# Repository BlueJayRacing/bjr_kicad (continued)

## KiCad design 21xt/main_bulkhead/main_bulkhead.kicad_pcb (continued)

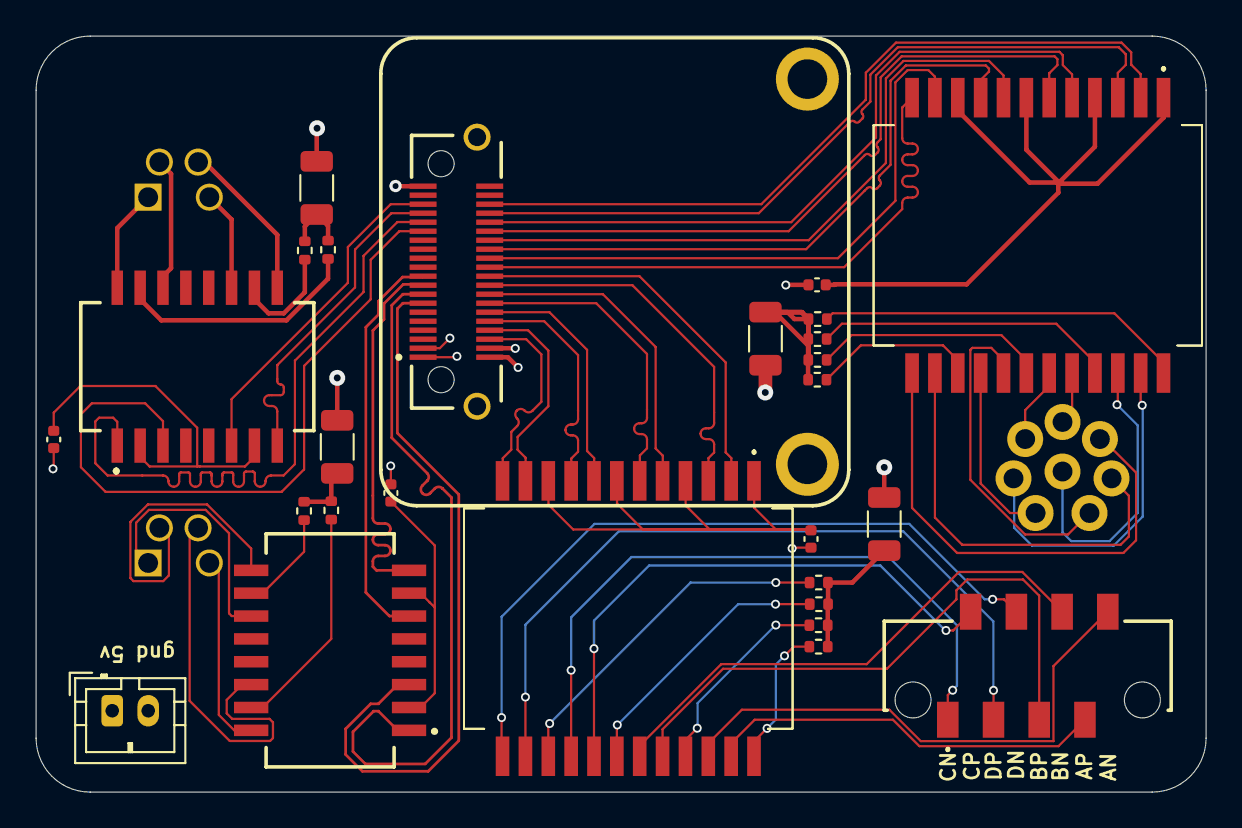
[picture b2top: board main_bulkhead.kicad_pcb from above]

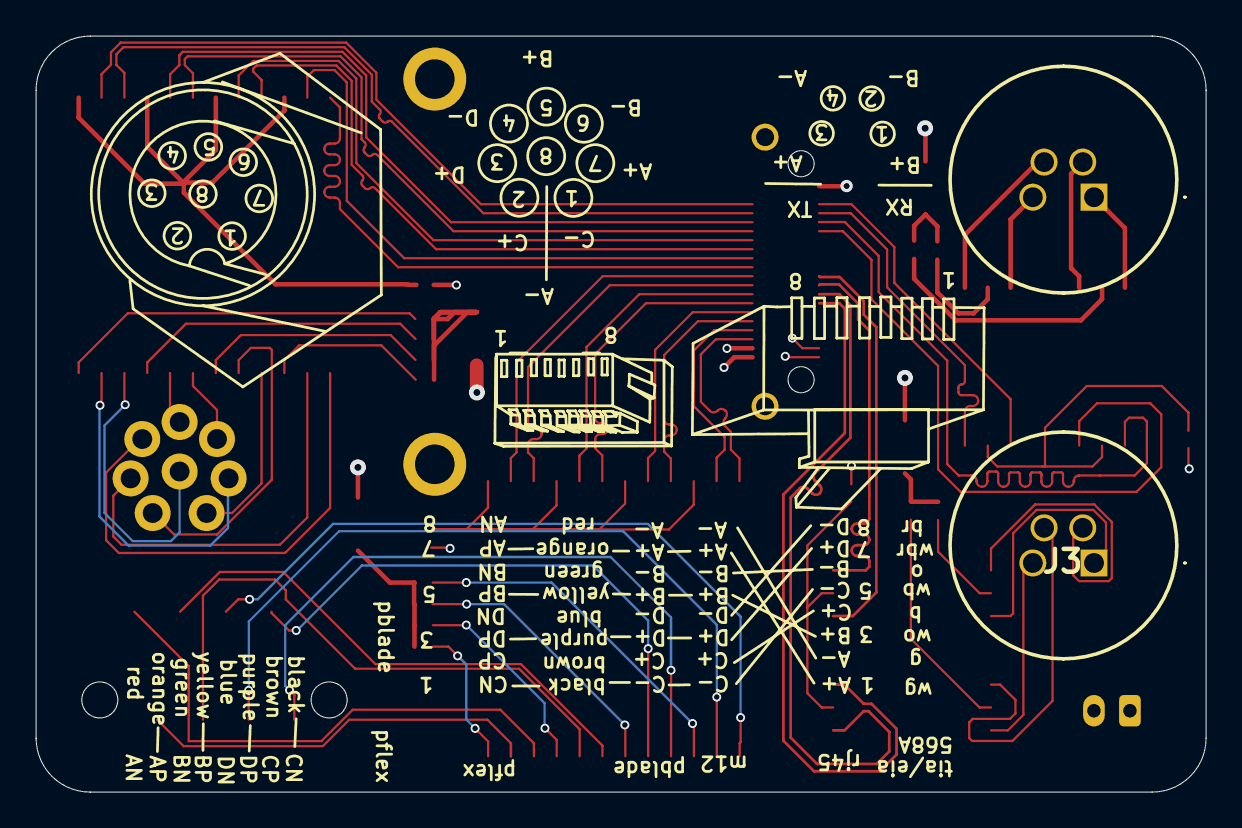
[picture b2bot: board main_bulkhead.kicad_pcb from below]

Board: 4 copper layers, 65.0 x 42.0 mm, 30 parts (3 on the bottom side), 70 nets.

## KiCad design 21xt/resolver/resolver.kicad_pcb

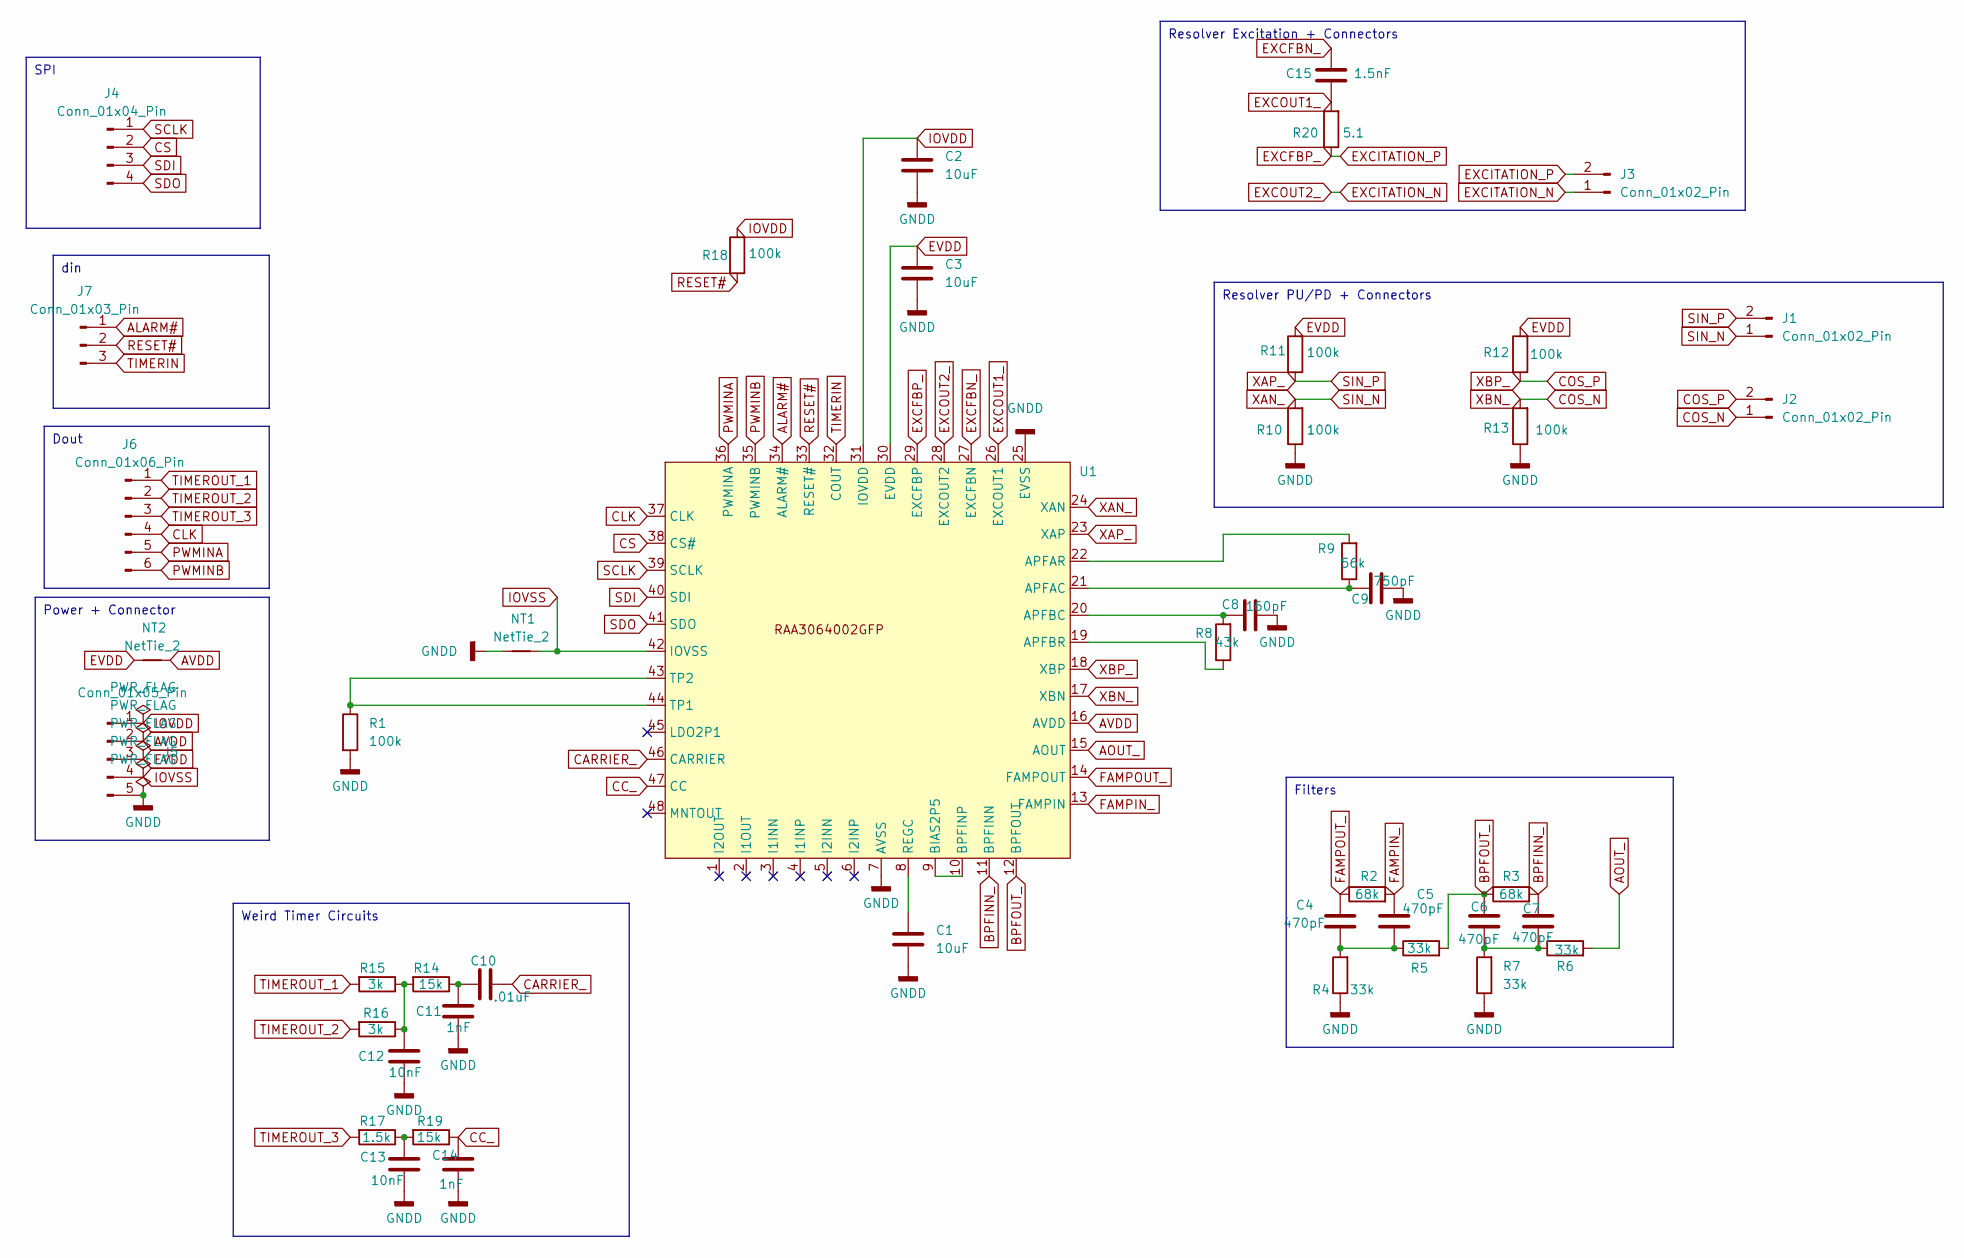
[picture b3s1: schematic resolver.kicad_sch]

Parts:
C1: 10uF; C_0201_0603Metric
C2, C3: 10uF; C_0201_0603Metric_Pad0.64x0.40mm_HandSolder
C4, C5, C6, C7: 470pF; C_0201_0603Metric_Pad0.64x0.40mm_HandSolder
C8: 160pF; C_0201_0603Metric_Pad0.64x0.40mm_HandSolder
C9: 750pF; C_0201_0603Metric_Pad0.64x0.40mm_HandSolder
C10: .01uF; C_0201_0603Metric_Pad0.64x0.40mm_HandSolder
C11, C14: 1nF; C_0201_0603Metric_Pad0.64x0.40mm_HandSolder
C12, C13: 10nF; C_0201_0603Metric_Pad0.64x0.40mm_HandSolder
C15: 1.5nF; C_0201_0603Metric_Pad0.64x0.40mm_HandSolder
J1, J2, J3: Conn_01x02_Pin; PinHeader_1x02_P2.54mm_Vertical
J4: Conn_01x04_Pin; PinHeader_1x04_P2.54mm_Vertical
J5: Conn_01x05_Pin; PinHeader_1x05_P2.54mm_Vertical
J6: Conn_01x06_Pin; PinHeader_1x06_P2.54mm_Vertical
J7: Conn_01x03_Pin; PinHeader_1x03_P2.54mm_Vertical
NT1, NT2: NetTie_2; SolderJumper-2_P1.3mm_Bridged2Bar_Pad1.0x1.5mm
R1, R10, R11, R12, R13, R18: 100k; R_0201_0603Metric
R2, R3: 68k; R_0201_0603Metric
R4, R5, R6, R7: 33k; R_0201_0603Metric
R8: 43k; R_0201_0603Metric
R9: 56k; R_0201_0603Metric
R14, R19: 15k; R_0201_0603Metric
R15, R16: 3k; R_0201_0603Metric
R17: 1.5k; R_0201_0603Metric
R20: 5.1; R_0201_0603Metric
U1: LQFP-48_7x7mm_P0.5mm

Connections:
ALARM#: J7.1, U1.34 (ALARM#)
AOUT_: R6.2, U1.15 (AOUT)
AVDD: J5.2, NT2.2, U1.16 (AVDD)
BPFINN_: C7.1, R3.2, U1.11 (BPFINN)
BPFOUT_: C6.1, R3.1, R5.2, U1.12 (BPFOUT)
CARRIER_: C10.2, U1.46 (CARRIER)
CC_: C14.2, R19.1, U1.47 (CC)
CLK: J6.4, U1.37 (CLK)
COS_N: J2.1, R13.2, U1.17 (XBN)
COS_P: J2.2, R12.1, U1.18 (XBP)
CS: J4.2, U1.38 (CS#)
EVDD: C3.1, J5.3, NT2.1, R11.2, R12.2, U1.30 (EVDD)
EXCFBN_: C15.2, U1.27 (EXCFBN)
EXCFBP_: J3.2, R20.1, U1.29 (EXCFBP)
EXCITATION_N: J3.1, U1.28 (EXCOUT2)
EXCOUT1_: C15.1, R20.2, U1.26 (EXCOUT1)
FAMPIN_: C5.1, R2.2, U1.13 (FAMPIN)
FAMPOUT_: C4.1, R2.1, U1.14 (FAMPOUT)
GNDD: C1.2, C2.2, C3.2, C8.2, C9.2, C11.1, C12.1, C13.1, C14.1, J5.5, NT1.1, R1.2, R4.1, R7.1, R10.1, R13.1, U1.7 (AVSS), U1.25 (EVSS)
IOVDD: C2.1, J5.1, R18.2, U1.31 (IOVDD)
IOVSS: J5.4, NT1.2, U1.42 (IOVSS)
unnamed: C4.2, C5.2, R4.2, R5.1
unnamed: C6.2, C7.2, R6.1, R7.2
unnamed: C10.1, C11.2, R14.1
unnamed: C12.2, R14.2, R15.1, R16.1
unnamed: C13.2, R17.1, R19.2
unnamed: C9.1, R9.1, U1.21 (APFAC)
unnamed: R9.2, U1.22 (APFAR)
unnamed: C8.1, R8.2, U1.20 (APFBC)
unnamed: R8.1, U1.19 (APFBR)
unnamed: U1.9 (BIAS2P5), U1.10 (BPFINP)
unnamed: C1.1, U1.8 (REGC)
unnamed: R1.1, U1.43 (TP2), U1.44 (TP1)
PWMINA: J6.5, U1.36 (PWMINA)
PWMINB: J6.6, U1.35 (PWMINB)
RESET#: J7.2, R18.1, U1.33 (RESET#)
SCLK: J4.1, U1.39 (SCLK)
SDI: J4.3, U1.40 (SDI)
SDO: J4.4, U1.41 (SDO)
SIN_N: J1.1, R10.2, U1.24 (XAN)
SIN_P: J1.2, R11.1, U1.23 (XAP)
TIMERIN: J7.3, U1.32 (COUT)
TIMEROUT_1: J6.1, R15.2
TIMEROUT_2: J6.2, R16.2
TIMEROUT_3: J6.3, R17.2

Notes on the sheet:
Weird Timer Circuits
Filters
Resolver Excitation + Connectors
Power + Connector
SPI
Dout
Resolver PU/PD + Connectors
din

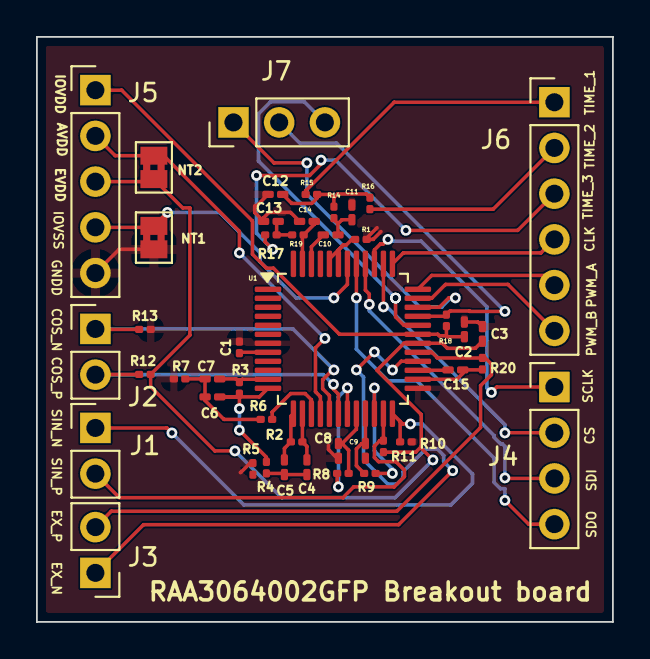
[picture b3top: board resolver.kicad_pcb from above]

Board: 2 copper layers, 32.0 x 32.5 mm, 45 parts (0 on the bottom side), 45 nets.

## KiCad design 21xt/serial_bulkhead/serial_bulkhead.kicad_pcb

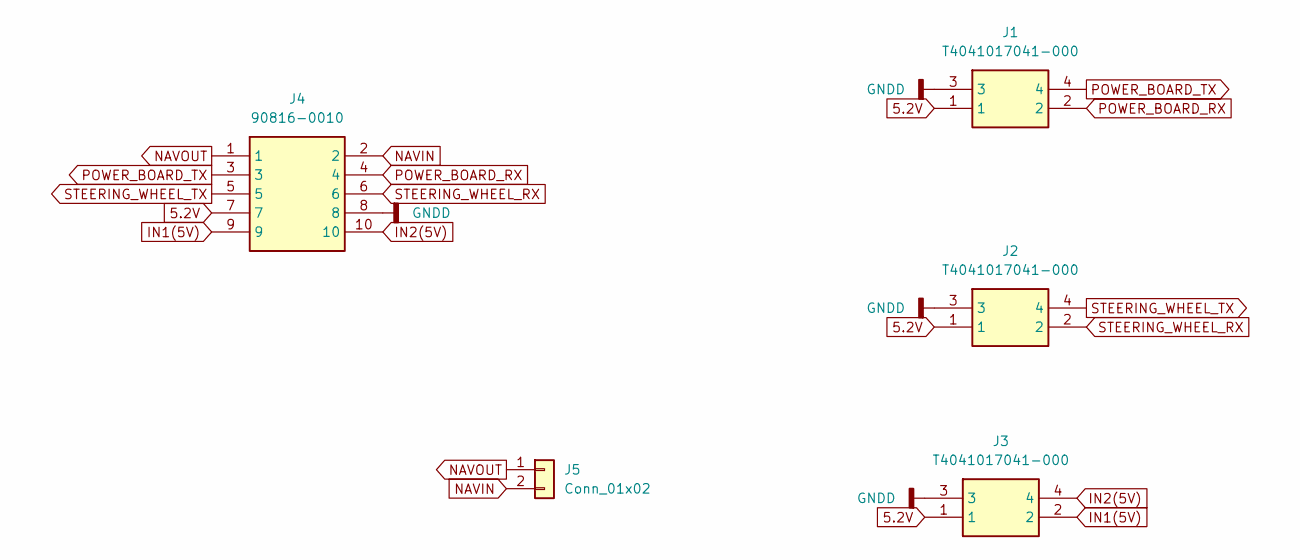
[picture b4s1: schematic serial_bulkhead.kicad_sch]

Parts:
J1, J2, J3: T4041017041-000; T4041017041000; Mouser Part Number 571-T4041017041-000
J4: 90816-0010; 908160010; Mouser Part Number 538-90816-0010
J5: Conn_01x02; JST_XH_B2B-XH-AM_1x02_P2.50mm_Vertical

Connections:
5.2V: J1.1, J2.1, J3.1, J4.7
GNDD: J1.3, J2.3, J3.3, J4.8
IN1(5V): J3.2, J4.9
IN2(5V): J3.4, J4.10
NAVIN: J4.2, J5.2
NAVOUT: J4.1, J5.1
POWER_BOARD_RX: J1.2, J4.4
POWER_BOARD_TX: J1.4, J4.3
STEERING_WHEEL_RX: J2.2, J4.6
STEERING_WHEEL_TX: J2.4, J4.5

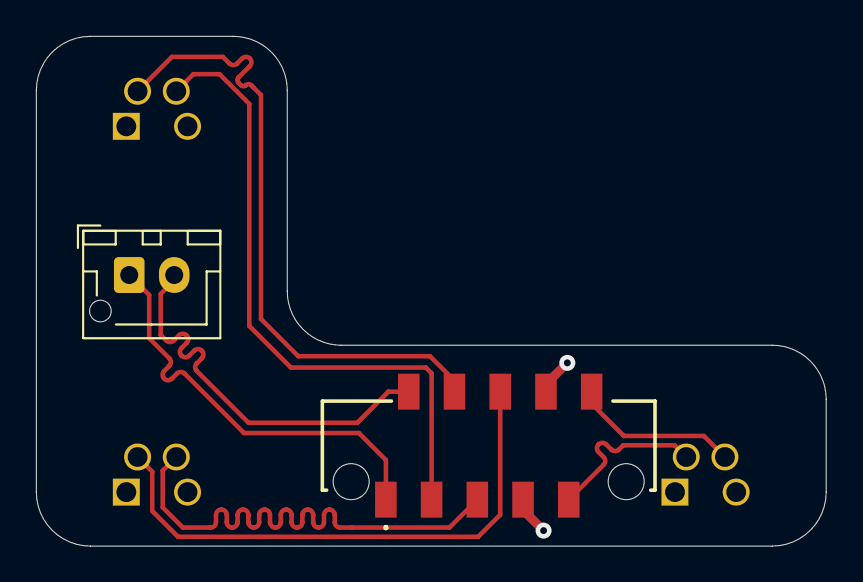
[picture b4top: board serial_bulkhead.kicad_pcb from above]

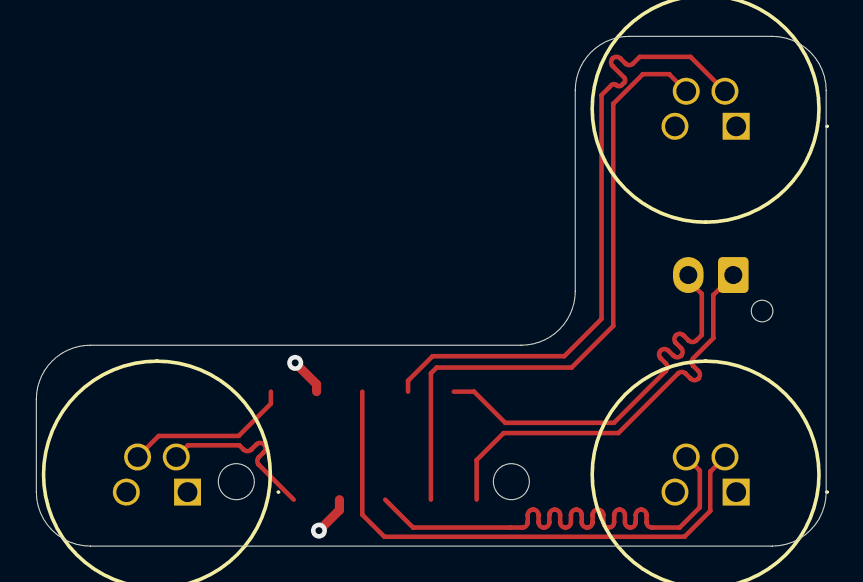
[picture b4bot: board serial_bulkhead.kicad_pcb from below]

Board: 4 copper layers, 43.9 x 28.3 mm, 5 parts (3 on the bottom side), 10 nets.

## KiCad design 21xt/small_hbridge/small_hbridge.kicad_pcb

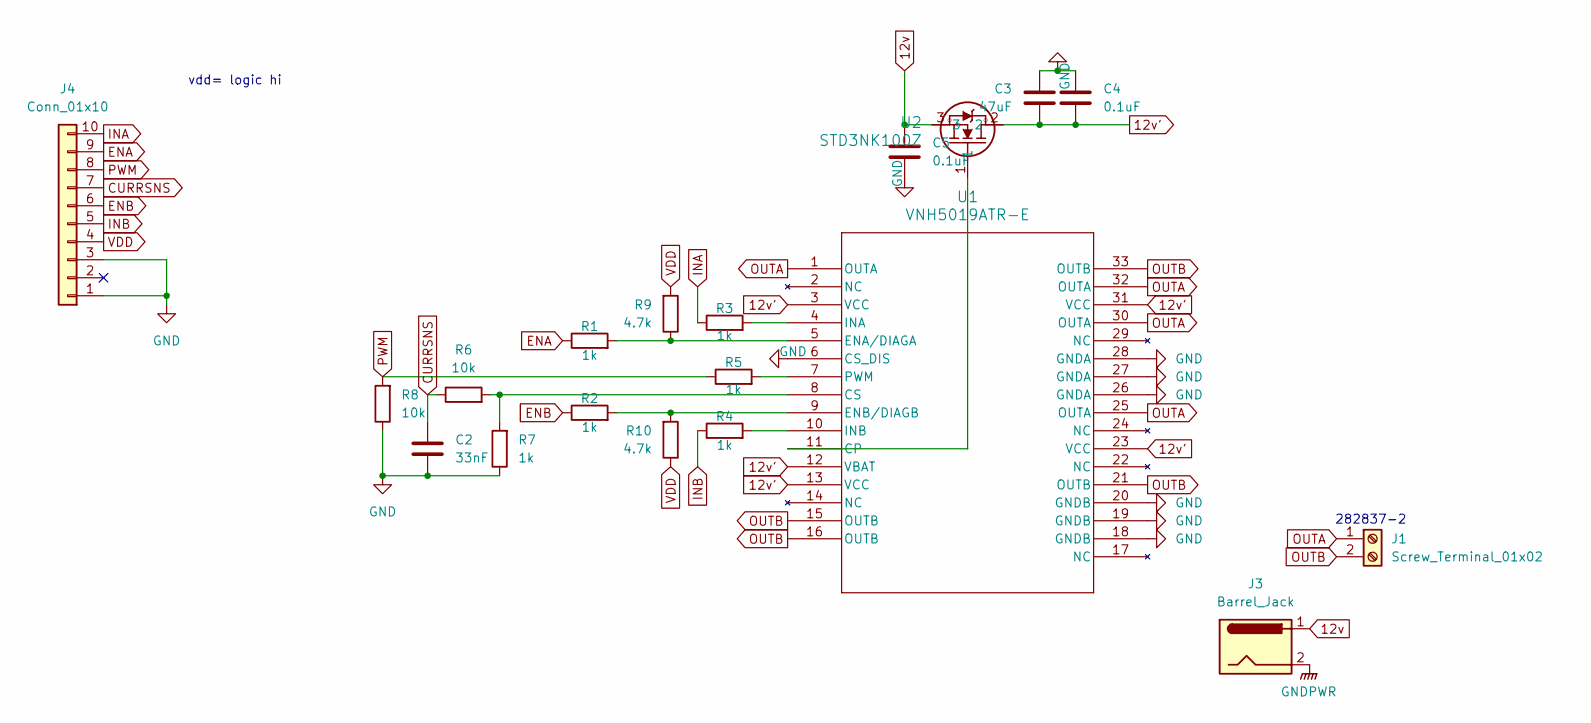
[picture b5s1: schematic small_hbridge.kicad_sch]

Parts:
C2: 33nF; C_0603_1608Metric
C3: 47uF; C_0603_1608Metric
C4, C5: 0.1uF; C_0603_1608Metric
J1: Screw_Terminal_01x02; 282837-2_TYC
J3: Barrel_Jack; CUI_PJ-037A
J4: Conn_01x10; PinHeader_1x10_P2.54mm_Vertical
R1, R2, R3, R4, R5, R7: 1k; R_0603_1608Metric
R6, R8: 10k; R_0603_1608Metric
R9, R10: 4.7k; R_0603_1608Metric
U1: VNH5019ATR-E; MultiPowerSO-30_STM
U2: STD3NK100Z; DPAK_STM

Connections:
12v: C5.2, J3.1, U2.3
12v': C3.2, C4.2, U1.3 (VCC), U1.12 (VBAT), U1.13 (VCC), U1.23 (VCC), U1.31 (VCC), U2.2
CURRSNS: C2.1, J4.7, R6.1
ENA: J4.9, R1.1
ENB: J4.6, R2.1
GND: C2.2, C3.1, C4.1, C5.1, J4.1, J4.3, R7.1, R8.1, U1.6 (CS_DIS), U1.18 (GNDB), U1.19 (GNDB), U1.20 (GNDB), U1.26 (GNDA), U1.27 (GNDA), U1.28 (GNDA)
GNDPWR: J3.2
INA: J4.10, R3.1
INB: J4.5, R4.1
unnamed: U1.11 (CP), U2.1
unnamed: R6.2, R7.2, U1.8 (CS)
unnamed: R1.2, R9.1, U1.5 (ENA/DIAGA)
unnamed: R2.2, R10.2, U1.9 (ENB/DIAGB)
unnamed: R3.2, U1.4 (INA)
unnamed: R4.2, U1.10 (INB)
unnamed: R5.2, U1.7 (PWM)
OUTA: J1.1, U1.1 (OUTA), U1.25 (OUTA), U1.30 (OUTA), U1.32 (OUTA)
OUTB: J1.2, U1.15 (OUTB), U1.16 (OUTB), U1.21 (OUTB), U1.33 (OUTB)
PWM: J4.8, R5.1, R8.2
VDD: J4.4, R9.2, R10.1

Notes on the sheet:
vdd= logic hi
282837-2

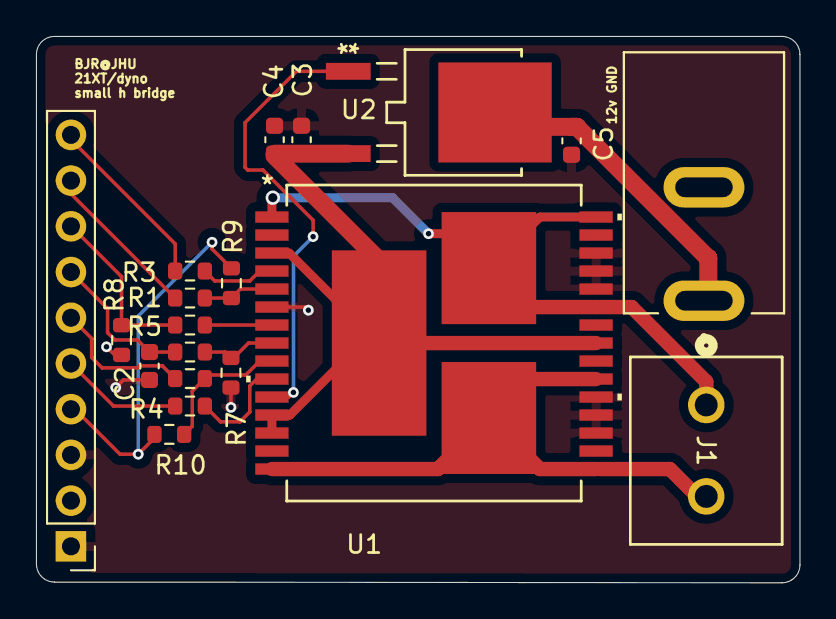
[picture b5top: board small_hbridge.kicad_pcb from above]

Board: 2 copper layers, 42.4 x 30.4 mm, 19 parts (0 on the bottom side), 19 nets.

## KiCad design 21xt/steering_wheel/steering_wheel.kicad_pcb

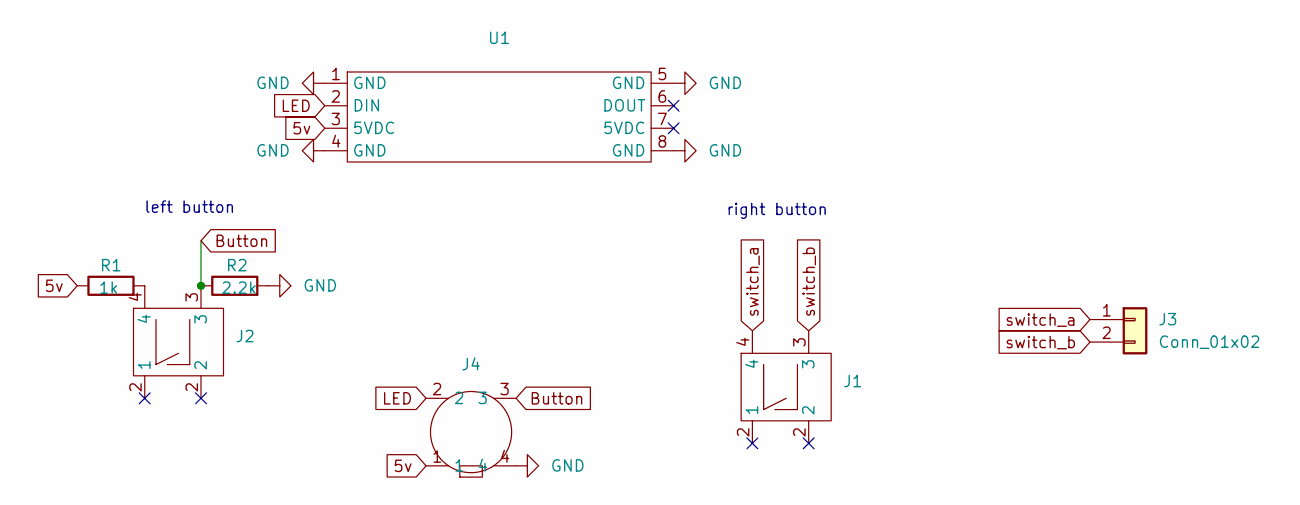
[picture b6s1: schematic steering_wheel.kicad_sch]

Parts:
J1, J2: K12SD S 1.5 6N O LFTX
J3: Conn_01x02; SolderWire-0.1sqmm_1x02_P3.6mm_D0.4mm_OD1mm
J4: m8 pp bulkhead 09 4912 081 04
R1: 1k; R_0402_1005Metric
R2: 2.2k; R_0402_1005Metric
U1: led_strip

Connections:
5v: J4.1, R1.1, U1.3 (5VDC)
Button: J2.3, J4.3, R2.1
GND: J4.4, R2.2, U1.1 (GND), U1.4 (GND), U1.5 (GND), U1.8 (GND)
LED: J4.2, U1.2 (DIN)
unnamed: J2.4, R1.2
switch_a: J1.4, J3.1
switch_b: J1.3, J3.2

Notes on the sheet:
right button
left button

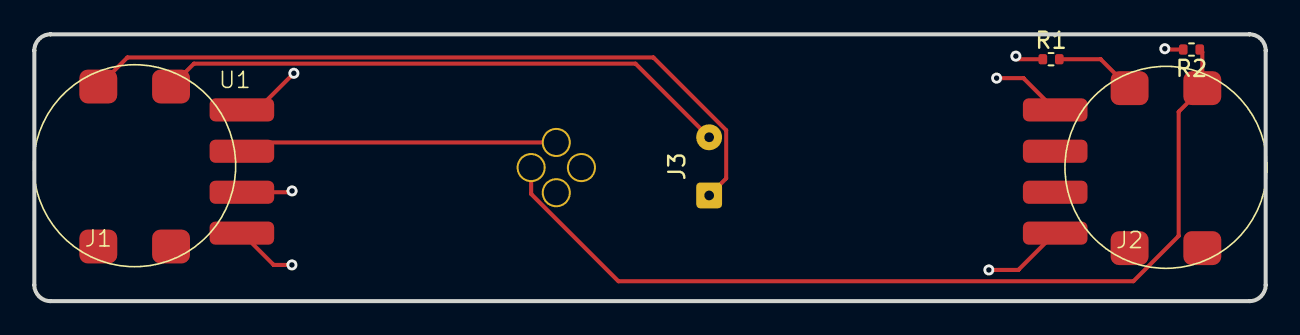
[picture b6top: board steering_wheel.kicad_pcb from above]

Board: 4 copper layers, 76.2 x 16.5 mm, 7 parts (1 on the bottom side), 7 nets.
